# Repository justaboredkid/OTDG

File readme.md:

# Open Tactile Data Glove

In NO way this is PRODUCTION READY.

**O**pen **T**actile **D**ata **G**love, or **OTDG** for short, is a glove that senses tactile feedback. 

O is for **O**pen, which means that the glove is OPEN SOURCED. It is under the SolderPad hardware license v2.0 (Which is a warp around of the Apache 2.0 License), and it allows a “*perpetual, worldwide, non-exclusive, no-charge, royalty-free, irrevocable license under the Rights to reproduce, prepare Derivative Works of, make, adapt, repair, publicly display, publicly perform, sublicense, and distribute the Work and such Derivative Works in Source or Object form and do anything in relation to the Work as if the Rights did not exist.*”

T is for **T**actile, where it describes the main purpose of the glove: to interpret tactile data. Even though the project was created for my science project (ASL interpretation), its use is far beyond just that. It can provide basic hand input for VR/AR purposes, robotic control, and it can also, if you write the software for it, emulate a mouse or something. It’s up to anyone. The foundations are here.

D is for **D**ata, describing that the glove is not a computation device on its own. It is only peripheral device. The current version of OTDG connects directly to a Raspberry Pi Zero. If you bought the wireless version of the RPi Zero (The RPi Zero W), it can expand the functionality of the glove by connecting to a phone and providing inertial sensor data. Future expansions might integrate the sensors inside the glove itself, but it does no processing on its own.

G is for **G**love. IT IS A GLOVE, what did you expect?

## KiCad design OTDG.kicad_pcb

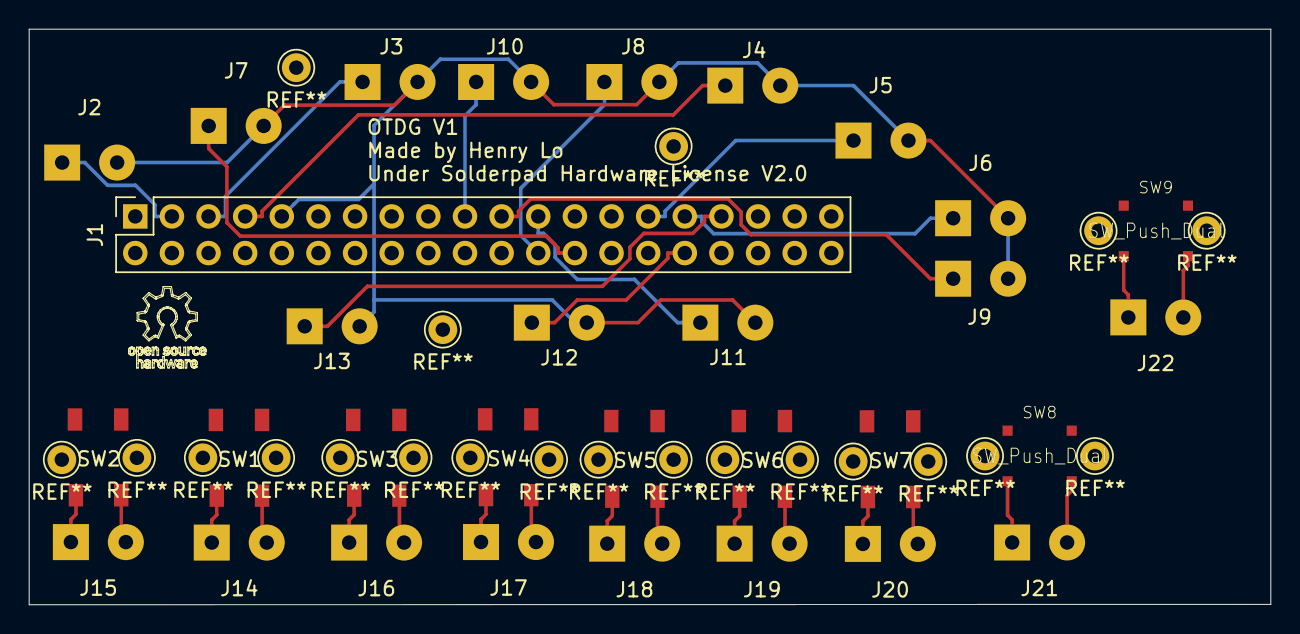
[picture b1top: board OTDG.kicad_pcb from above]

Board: 2 copper layers, 86.1 x 39.9 mm, 31 parts (0 on the bottom side), 31 nets.

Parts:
J1: Raspberry_Pi_2_3; PinSocket_2x20_P2.54mm_Vertical
J2, J3, J4, J5, J6, J7, J8, J9, J10, J11, J12, J13: Conn_01x02_Female; SolderWirePad_1x02_P3.81mm_Drill1mm
J14, J15, J16, J17, J18, J19, J20, J21, J22: Conn_01x02_Male; SolderWirePad_1x02_P3.81mm_Drill1mm
SW1, SW2, SW3, SW4, SW5, SW6, SW7: SW_Push_Dual; PTS647
SW8, SW9: SW_Push_Dual; TL3315NF100Q

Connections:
GND: J1.9, J2.2, J3.2, J4.2, J5.2, J6.2, J7.2, J8.2, J9.2, J10.2, J11.2, J12.2, J13.2
GPIO2: J1.3, J2.1
GPIO3: J1.5, J3.1
GPIO4: J1.7, J4.1
GPIO5: J1.29, J5.1
GPIO6: J1.31, J6.1
GPIO7: J1.26, J7.1
GPIO8: J1.24, J8.1
GPIO9: J1.21, J9.1
GPIO10: J1.19, J10.1
GPIO11: J1.23, J11.1
GPIO12: J1.32, J12.1
GPIO13: J1.33, J13.1
unnamed: J14.1, SW1.3
unnamed: J14.2, SW1.4
unnamed: J15.1, SW2.3
unnamed: J15.2, SW2.4
unnamed: J16.1, SW3.3
unnamed: J16.2, SW3.4
unnamed: J17.1, SW4.3
unnamed: J17.2, SW4.4
unnamed: J18.1, SW5.3
unnamed: J18.2, SW5.4
unnamed: J19.1, SW6.3
unnamed: J19.2, SW6.4
unnamed: J20.1, SW7.3
unnamed: J20.2, SW7.4
unnamed: J21.1, SW8.3
unnamed: J21.2, SW8.4
unnamed: J22.1, SW9.3
unnamed: J22.2, SW9.4

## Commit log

2019-06-09 Connected ground, added README

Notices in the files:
OTDG.kicad_pcb:
Under Solderpad Hardware License V2.0
